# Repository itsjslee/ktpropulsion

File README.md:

# ktpropulsion

KiCad 10 project for a Teensy 4.1, BMP180 module, and MPU6050 module with onboard logging.

Open `KTPropulsion.kicad_pro` in KiCad. Custom symbols, footprints, and the switch 3D model are stored in this repository and use project-relative library paths. Standard KiCad libraries are also required.

## Save a revision

Save the schematic and board in KiCad first, then run these commands in this folder:

```sh
git status
git add KTPropulsion.kicad_sch KTPropulsion.kicad_pcb KTPropulsion.kicad_pro libraries 3dmodels fp-lib-table sym-lib-table README.md .gitignore
git diff --cached --stat
git commit -m "Describe the design change"
```

Use `git log --oneline` to view checkpoints. Create an experiment branch with `git switch -c experiment-name`.

KiCad local state, automatic backups, routing experiments, and generated Gerber/DRC outputs are ignored. For fabrication, export fresh Gerbers and drills from a saved and checked revision; retain the ZIP with a Git release or separate archive. A commit records the design, not its fabrication approval.

Git history is local until a remote repository is configured and pushed. Close KiCad before restoring older design files to avoid overwriting them from an open editor.

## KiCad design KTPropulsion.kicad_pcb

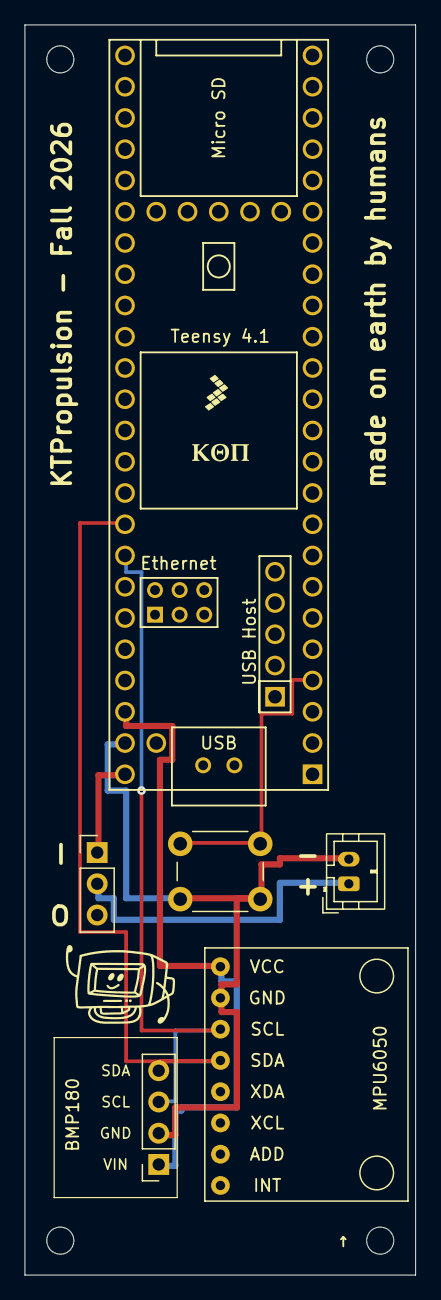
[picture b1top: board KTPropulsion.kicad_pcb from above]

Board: 2 copper layers, 31.8 x 101.6 mm, 7 parts (0 on the bottom side), 7 nets.

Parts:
J1: BATTERY_1S; JST_PH_B2B-PH-K_1x02_P2.00mm_Vertical
J2: BMP180; BMP180_21x18_Socket_1x04
SW1: SW_SPDT; PinHeader_1x03_P2.54mm_Vertical
SW2: SW_Push; SW_PUSH_6mm
U1: Teensy 4.1; Teensy41
U3: MPU6050; module_mpu6050
↑  : H3; MountingHole_2.2mm_M2

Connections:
/+3V3: J2.1, U1.46 (3V3), U3.1 (VCC)
/SCL: J2.3, U1.41 (19_A5_SCL), U3.3 (SCL)
/SDA: J2.4, U1.40 (18_A4_SDA), U3.4 (SDA)
unnamed: J1.1, SW1.2 (B)
unnamed: J1.2, J2.2, SW2.2, U1.47 (GND), U3.2 (GND)
unnamed: SW1.1 (A), U1.48 (VIN)
unnamed: SW2.1, U1.4 (2_OUT2)
